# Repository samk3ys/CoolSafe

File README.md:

# Cool Safe
UKY capstone project

ECE 490 / 491 - 2 Semester Senior Design - Fall 2019 thru Spring 2020

Sponsor: GE Appliances, a Haier Company 
Contact: Choon Jae-Ryu (ChoonJae.Ryu@geappliances.com)

Members: 
  Sam Keys (CPE) 
  Shae Henry (EE) 
  Steven Deaton (EE) 
  Sylvester Okafor (EE) 
  Tylor Mendez (CPE)

Project Summary: 
  Multi-generational living has driven a need for a safe storage for medications in the home. This project aims to develop a lock-bin for use in a refrigerator that is only accessible thru a biometric identification (or physical key for backup). Also to create a mobile app that can display authorized users and add / delete / disable these users.

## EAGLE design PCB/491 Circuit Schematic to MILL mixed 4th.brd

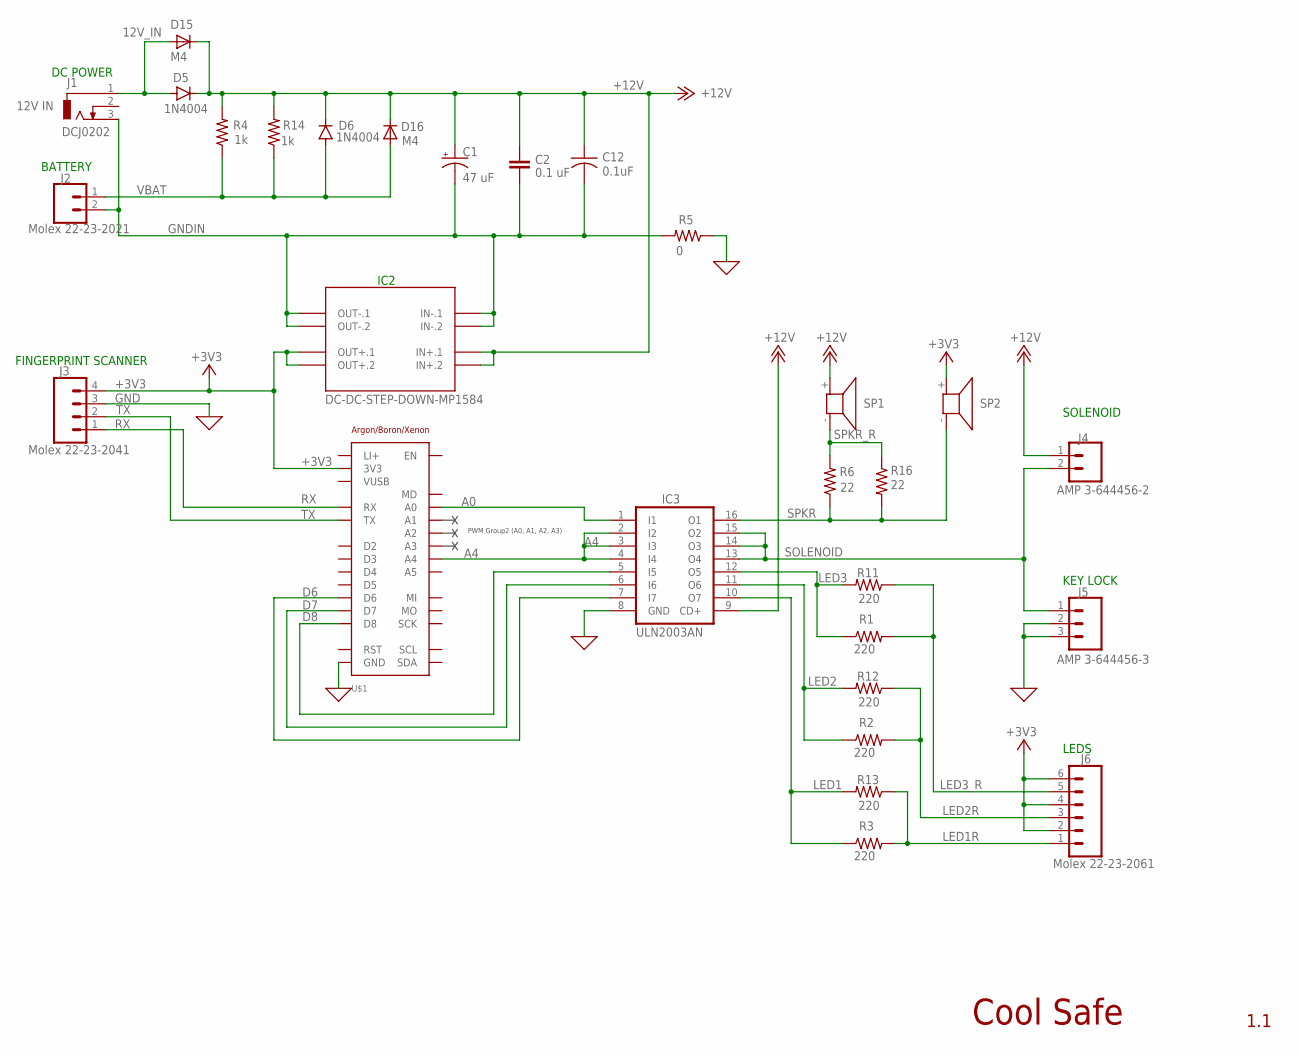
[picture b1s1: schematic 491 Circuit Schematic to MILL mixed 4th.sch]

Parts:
C1: 47 uF; E2,5-6
C2: 0.1 uF; C2.5-5
C12: 0.1uF; C1206
D5, D6: 1N4004; DO41-10
D15, D16: M4; SMA-DO214AC
IC2: DC-DC-STEP-DOWN-MP1584
IC3: ULN2003AN; DIL16
J1: DCJ0202
J2: Molex 22-23-2021; MOLEX-1X2
J3: Molex 22-23-2041; MOLEX-1X4
J4: AMP 3-644456-2; 1X02
J5: AMP 3-644456-3; 1X03
J6: Molex 22-23-2061; MOLEX-1X6
R1, R2, R3: 220; 0207/10
R4: 1k; 0207/10
R5: 0; 0207/10
R6: 22; 0204/7
R11, R12, R13: 220; M1206
R14: 1k; M1206
R16: 22; M1206
SP1, SP2: KSS1201
U$1: TEMPLATE_ARGON/BORON/XENONPTH; NO_PADS

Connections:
12V_IN: D5.A, D15.A, J1.1
+3V3: IC2.OUT+.1, IC2.OUT+.2, J3.4, J6.2, J6.4, J6.6, SP2.+ (1), U$1.P$14 (3V3)
+12V: C1.+, C2.1, C12.1, D5.C, D6.C, D15.K (C), D16.K (C), IC2.IN+.1, IC2.IN+.2, IC3.9 (CD+), J4.1, R4.2, R14.2, SP1.+ (1)
A0: IC3.1 (I1), U$1.P$17 (A0)
A4: IC3.2 (I2), IC3.3 (I3), IC3.4 (I4), U$1.P$21 (A4)
D6: IC3.7 (I7), U$1.P$6 (D6)
D7: IC3.6 (I6), U$1.P$5 (D7)
D8: IC3.5 (I5), U$1.P$4 (D8)
GND: IC3.8 (GND), J3.3, J5.2, J5.3, R5.1, U$1.P$16 (GND)
GNDIN: C1.-, C2.2, C12.2, IC2.IN-.1, IC2.IN-.2, IC2.OUT-.1, IC2.OUT-.2, J1.3, J2.2, R5.2
LED1: IC3.10 (O7), R3.1, R13.2
LED1R: J6.1, R3.2, R13.1
LED2: IC3.11 (O6), R2.1, R12.2
LED2R: J6.3, R2.2, R12.1
LED3: IC3.12 (O5), R1.1, R11.2
LED3_R: J6.5, R1.2, R11.1
RX: J3.1, U$1.P$26 (RX)
SOLENOID: IC3.13 (O4), IC3.14 (O3), IC3.15 (O2), J4.2, J5.1
SPKR: IC3.16 (O1), R6.1, R16.2, SP2.- (2)
SPKR_R: R6.2, R16.1, SP1.- (2)
TX: J3.2, U$1.P$27 (TX)
VBAT: D6.A, D16.A, J2.1, R4.1, R14.1

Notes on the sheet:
PWM Group2 (A0, A1, A2, A3)
1.1
Cool Safe
12V IN
SOLENOID
KEY LOCK
LEDS
BATTERY
FINGERPRINT SCANNER
IC2
DC POWER

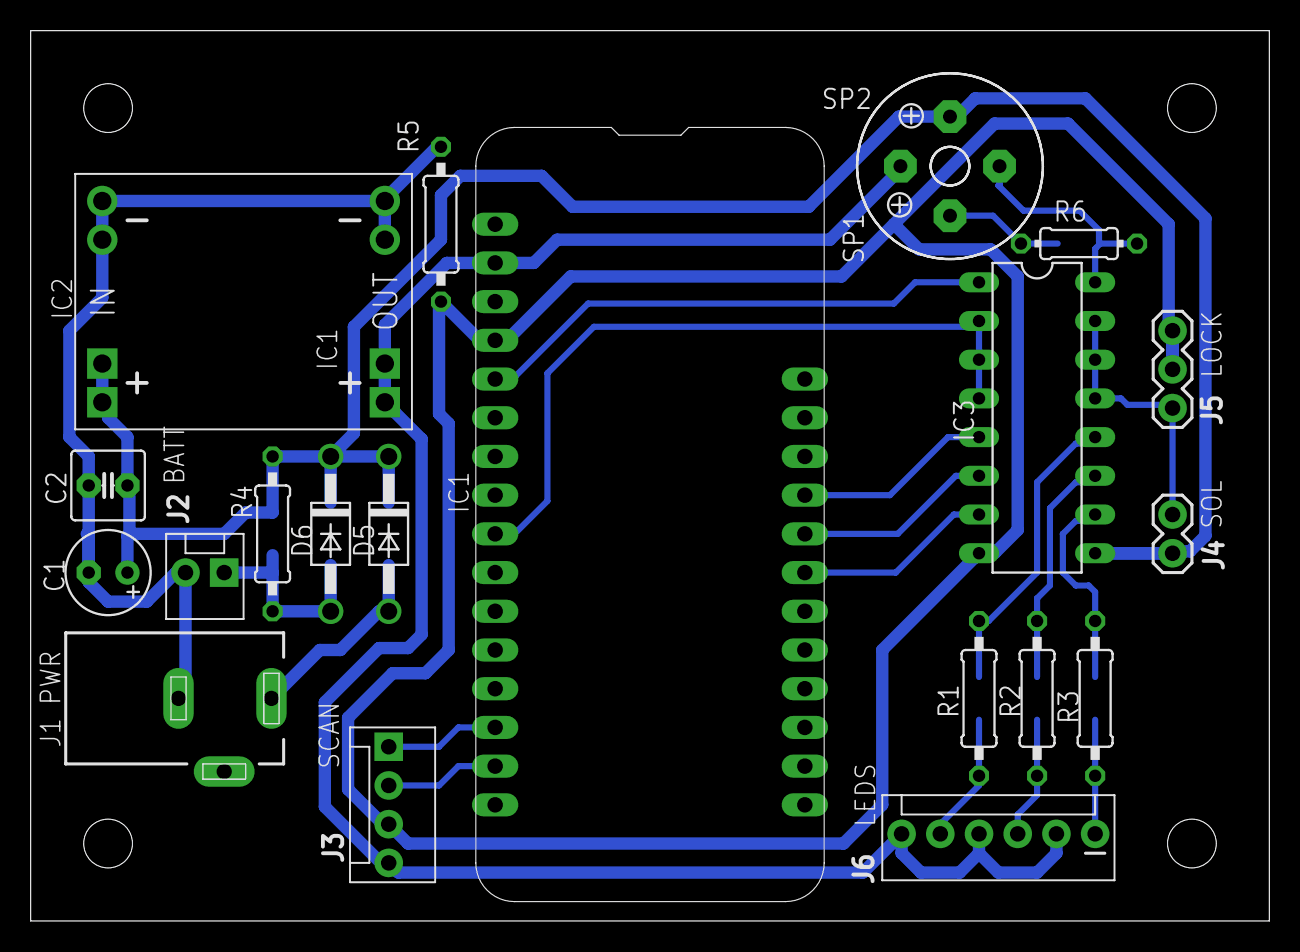
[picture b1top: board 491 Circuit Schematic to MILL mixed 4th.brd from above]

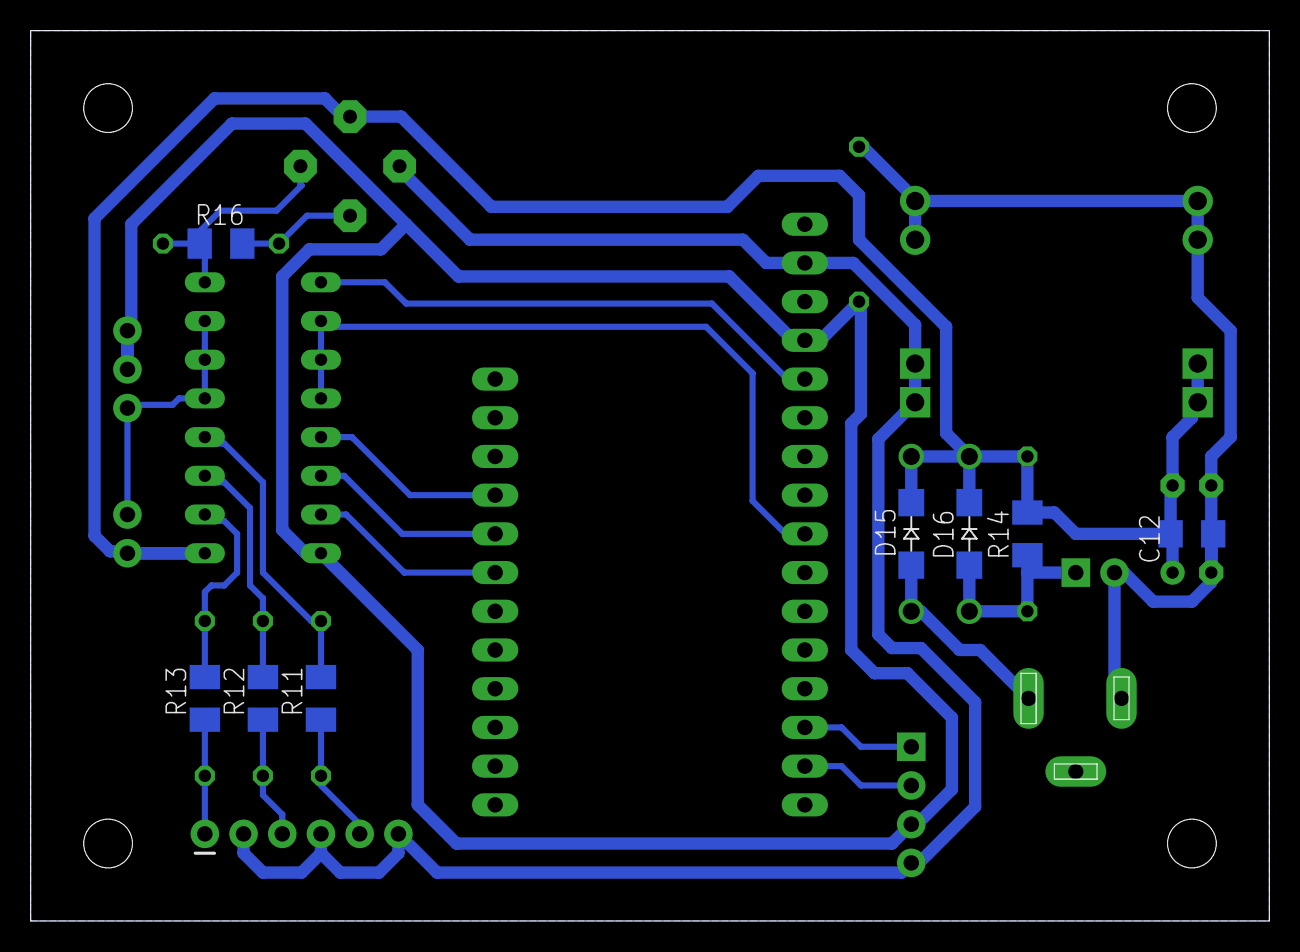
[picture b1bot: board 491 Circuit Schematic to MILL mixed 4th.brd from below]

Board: 2 copper layers, 81.3 x 58.4 mm, 29 parts (8 on the bottom side), 22 nets.

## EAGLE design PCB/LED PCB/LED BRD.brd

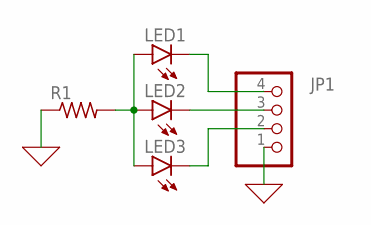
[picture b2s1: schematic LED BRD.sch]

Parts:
JP1: PINHD-1X4; 1X04
LED1, LED2, LED3: LED5MM
R1: R-US_0204/7; 0204/7

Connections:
0: JP1.1, R1.1
unnamed: LED1.A, LED2.A, LED3.A, R1.2
unnamed: JP1.2, LED3.K (C)
unnamed: JP1.4, LED1.K (C)
unnamed: JP1.3, LED2.K (C)

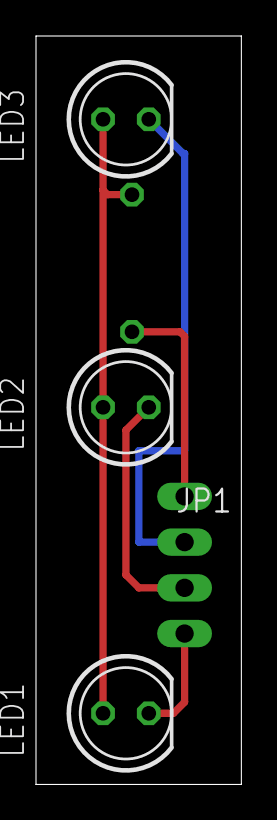
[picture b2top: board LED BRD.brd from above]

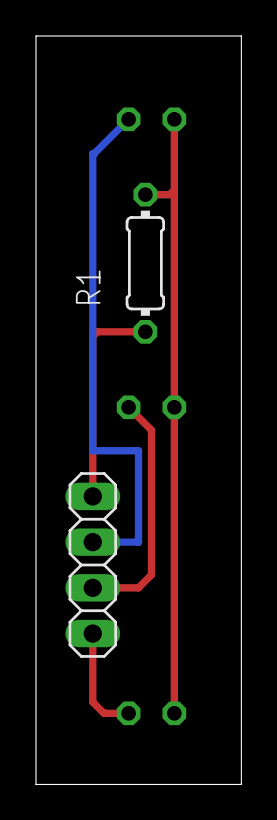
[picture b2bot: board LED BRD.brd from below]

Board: 2 copper layers, 11.4 x 41.6 mm, 5 parts (2 on the bottom side), 5 nets.

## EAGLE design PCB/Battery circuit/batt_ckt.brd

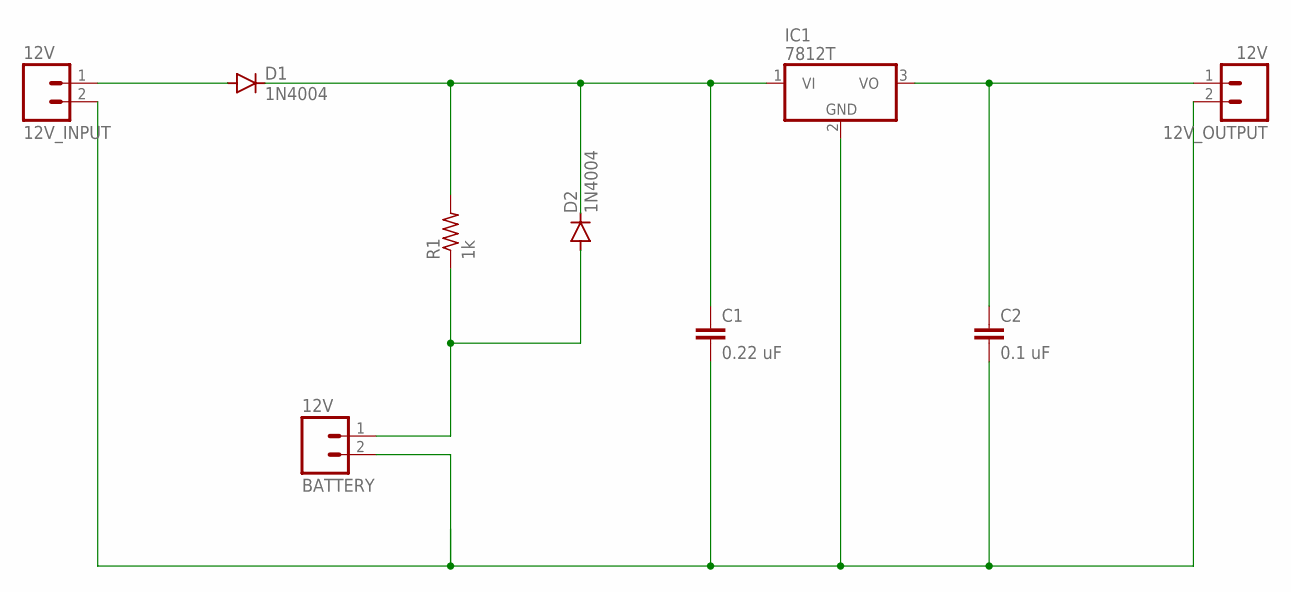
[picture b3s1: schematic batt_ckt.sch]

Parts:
12V_INPUT, 12V_OUTPUT: 12V; 02P
BATTERY: 12V; 02P
C1: 0.22 uF; C2.5-5
C2: 0.1 uF; C2.5-5
D1, D2: 1N4004; DO41-10
IC1: 7812T; TO220H
R1: 1k; 0207/10

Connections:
unnamed: BATTERY.1, D2.A, R1.1
unnamed: C1.1, D1.C, D2.C, IC1.1 (VI), R1.2
unnamed: 12V_INPUT.1, D1.A
unnamed: 12V_INPUT.2, 12V_OUTPUT.2, BATTERY.2, C1.2, C2.2, IC1.2 (GND)
unnamed: 12V_OUTPUT.1, C2.1, IC1.3 (VO)

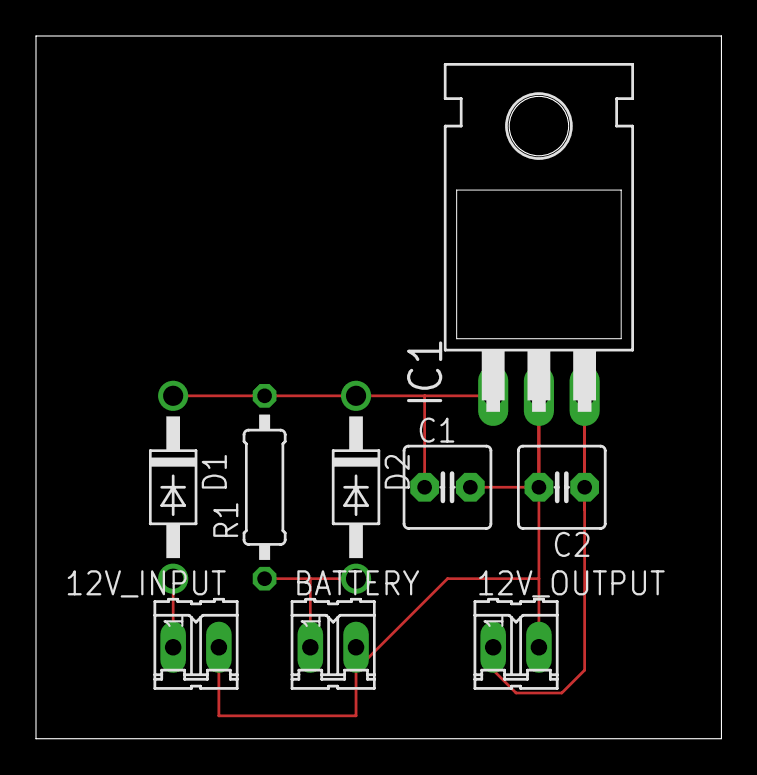
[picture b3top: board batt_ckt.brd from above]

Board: 2 copper layers, 38.1 x 39.0 mm, 9 parts (0 on the bottom side), 5 nets.

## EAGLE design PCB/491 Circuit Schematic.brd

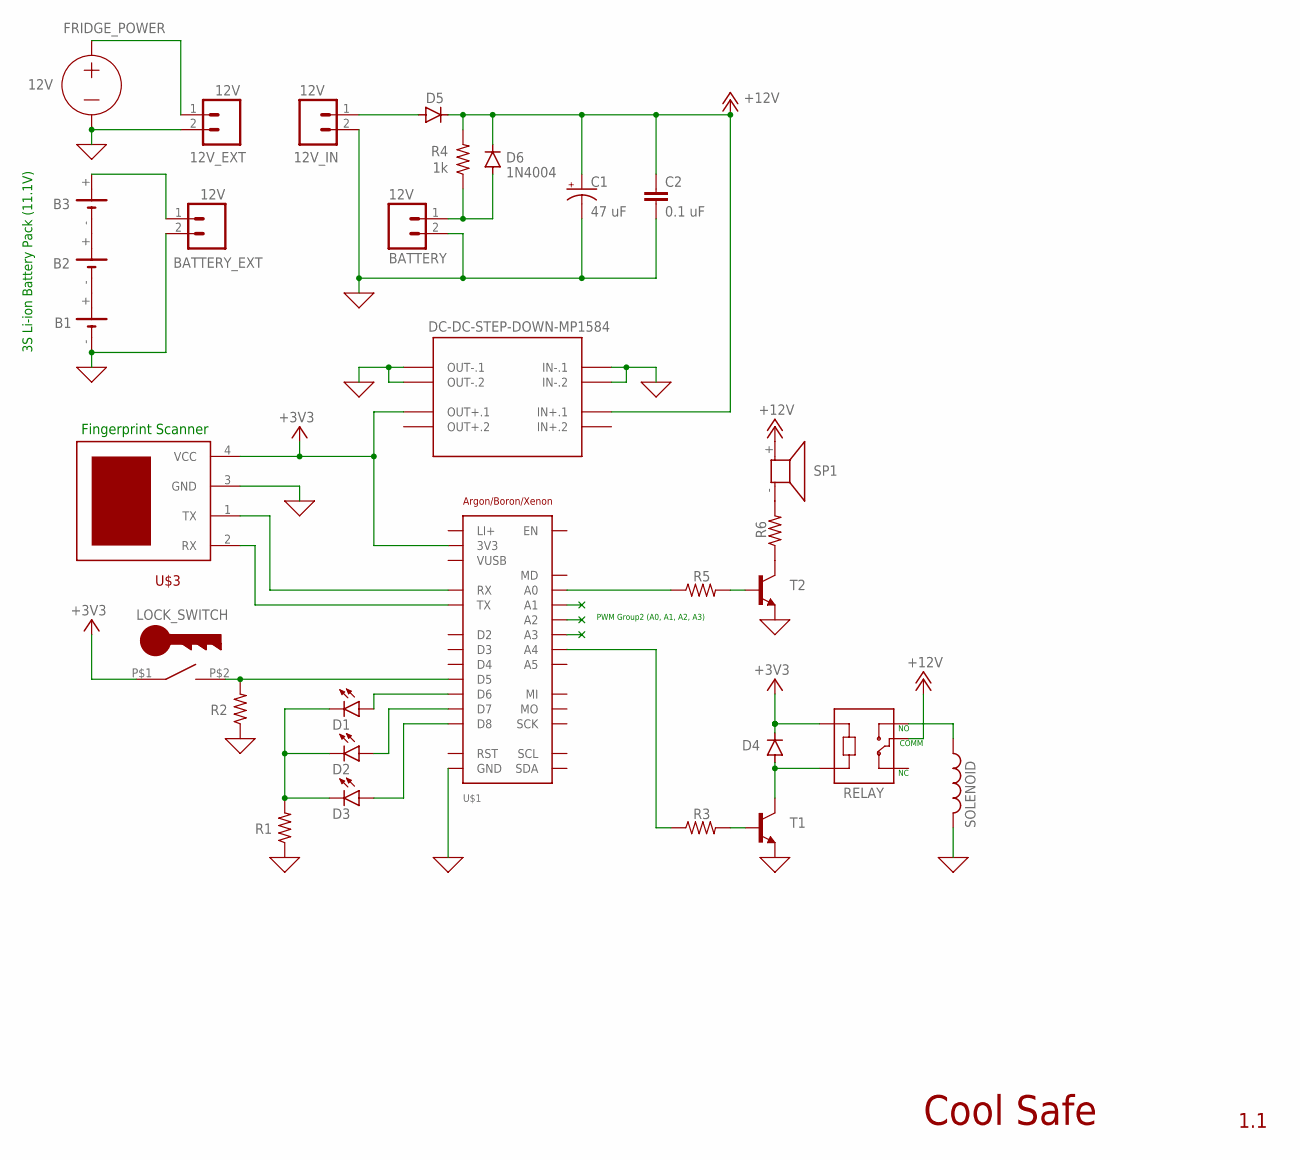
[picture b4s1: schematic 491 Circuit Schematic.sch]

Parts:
12V_EXT, 12V_IN: 12V; 02P
B1, B2, B3: SL-340/P3.6V
BATTERY: 12V; 02P
BATTERY_EXT: 12V; 02P
C1: 47 uF; E2,5-6
C2: 0.1 uF; C2.5-5
D1, D2, D3: U57X32
D4, D5, D6: 1N4004; DO41-10
L2: SOLENOID; 0207/5V
LOCK_SWITCH: LOCK_SWITCH; SWITCH_TERMINAL
R1, R2, R3, R5, R6: R-US_0204/7; 0204/7
R4: 1k; 0207/10
RELAY: SRD-05VDC-SL-C; RELAY_SRD-05VDC-SL-C
SP1: KSS1201
T1, T2: -NPN-TO92; TO92
U$1: TEMPLATE_ARGON/BORON/XENONFEATHER_ONLY; FEATHER_ONLY
U$2: DC-DC-STEP-DOWN-MP1584
U$3: FPS; JST

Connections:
0: 12V_EXT.2, 12V_IN.2, B1.-, BATTERY.2, BATTERY_EXT.2, C1.-, C2.2, L2.2, R1.1, R2.1, T1.1 (E), T2.1 (E), U$1.16B (GND), U$1.16T (GND), U$2.IN-.1, U$2.IN-.2, U$2.OUT-.1, U$2.OUT-.2, U$3.3 (GND)
+3V3: D4.C, LOCK_SWITCH.P$1, RELAY.A1, U$1.14B (3V3), U$1.14T (3V3), U$2.OUT+.1, U$3.4 (VCC)
FPS: R6.2, SP1.- (2)
unnamed: B2.+, B3.-
unnamed: R5.1, U$1.17B (A0), U$1.17T (A0)
unnamed: B1.+, B2.-
unnamed: D1.A, U$1.06B (D6), U$1.06T (D6)
unnamed: D2.A, U$1.05B (D7), U$1.05T (D7)
unnamed: D3.A, U$1.04B (D8), U$1.04T (D8)
unnamed: LOCK_SWITCH.P$2, R2.2, U$1.07B (D5), U$1.07T (D5)
unnamed: D1.K (C), D2.K (C), D3.K (C), R1.2
unnamed: D4.A, RELAY.A2, T1.3 (C)
unnamed: L2.1, RELAY.NO
unnamed: BATTERY.1, D6.A, R4.1
unnamed: U$1.26B (RX), U$1.26T (RX), U$3.1 (TX)
unnamed: R3.2, T1.2 (B)
unnamed: R3.1, U$1.21B (A4), U$1.21T (A4)
unnamed: U$1.18B (A1), U$1.18T (A1)
unnamed: U$1.19B (A2), U$1.19T (A2)
unnamed: U$1.20B (A3), U$1.20T (A3)
unnamed: U$1.27B (TX), U$1.27T (TX), U$3.2 (RX)
unnamed: 12V_IN.1, D5.A
unnamed: B3.+, BATTERY_EXT.1
unnamed: R6.1, T2.3 (C)

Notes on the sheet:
PWM Group2 (A0, A1, A2, A3)
COMM
Fingerprint Scanner
3S Li-ion Battery Pack (11.1V)
1.1
Cool Safe

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
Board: 2 copper layers, 28 parts (0 on the bottom side), 24 nets, no tracks yet.

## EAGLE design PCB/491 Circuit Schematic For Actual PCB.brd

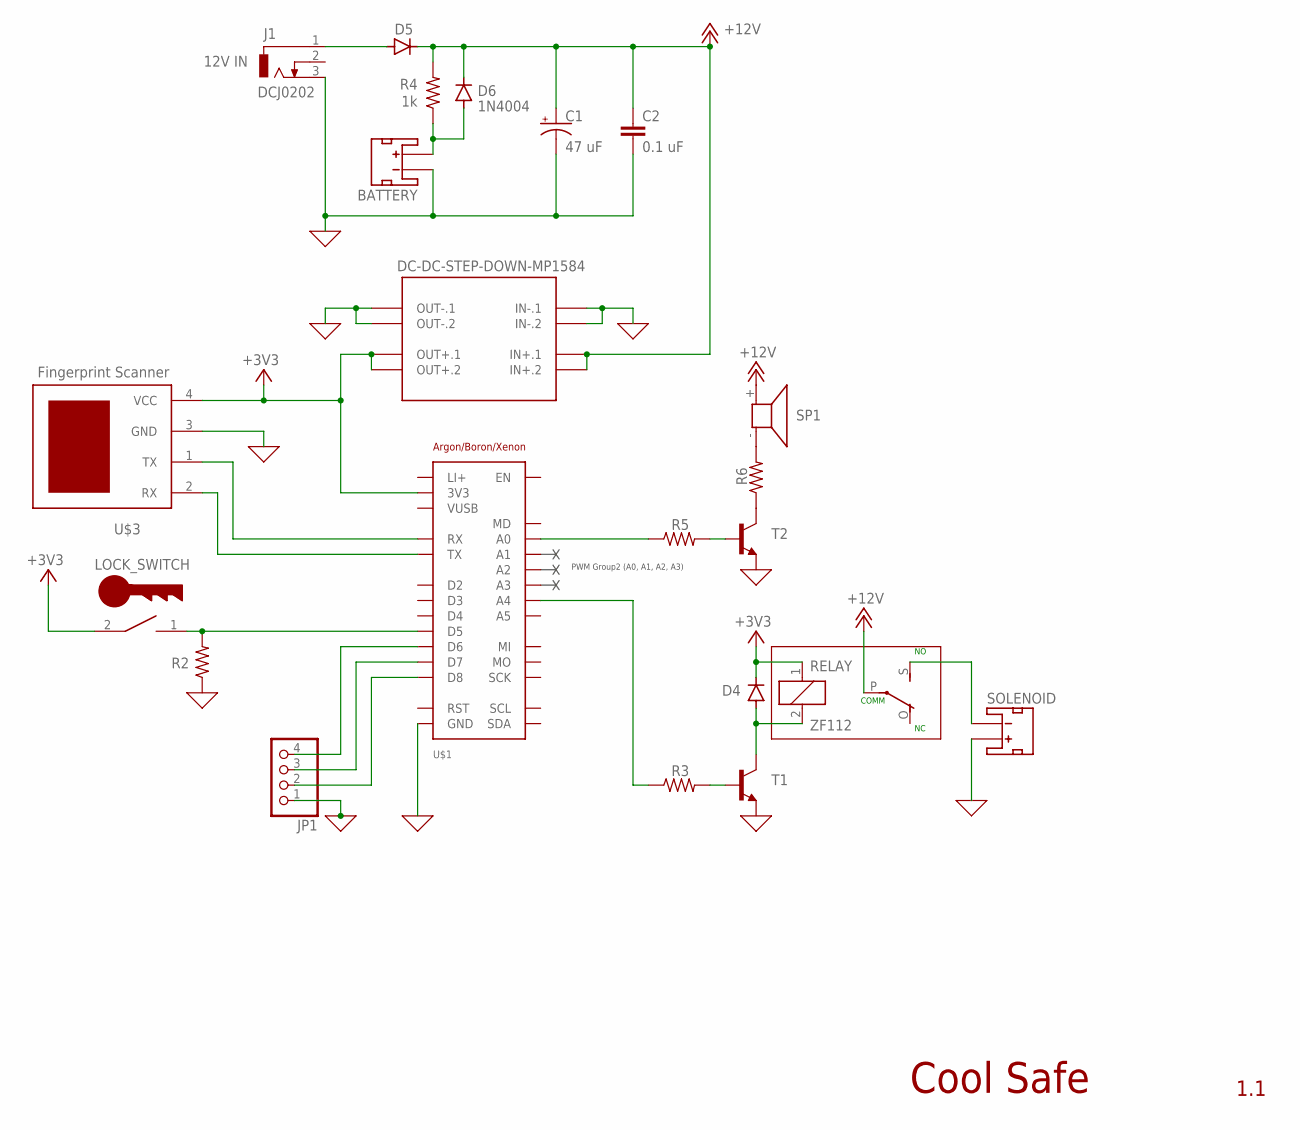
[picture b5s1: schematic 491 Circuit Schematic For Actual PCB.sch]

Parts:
BATTERY: JST_2MM_MALE; JST-2-SMD
C1: 47 uF; E2,5-6
C2: 0.1 uF; C2.5-5
D4, D5, D6: 1N4004; DO41-10
J1: DCJ0202
JP1: PINHD-1X4/90; 1X04/90
LOCK_SWITCH: LOCK_SWITCHSCREW_TERMINAL; 1751248
R2: R-US_0207/10; 0207/10
R3, R5, R6: R-US_0204/7; 0204/7
R4: 1k; 0207/10
RELAY: ZF112
SOLENOID: JST_2MM_MALE; JST-2-SMD
SP1: KSS1201
T1, T2: -NPN-TO92; TO92
U$1: TEMPLATE_ARGON/BORON/XENONFEATHER_ONLY; FEATHER_ONLY
U$2: DC-DC-STEP-DOWN-MP1584
U$3: FPSQWIIC; 1X04_1MM_RA

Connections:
0: BATTERY.1 (-), C1.-, C2.2, J1.3, JP1.1, R2.1, SOLENOID.2 (+), T1.1 (E), T2.1 (E), U$1.16B (GND), U$1.16T (GND), U$1.P$16 (GND), U$2.IN-.1, U$2.IN-.2, U$2.OUT-.1, U$2.OUT-.2, U$3.3 (GND)
+3V3: D4.C, LOCK_SWITCH.2, RELAY.1, U$1.14B (3V3), U$1.14T (3V3), U$1.P$14 (3V3), U$2.OUT+.1, U$2.OUT+.2, U$3.4 (VCC)
+12V: C1.+, C2.1, D5.C, D6.C, R4.2, RELAY.P, SP1.+ (1), U$2.IN+.1, U$2.IN+.2
unnamed: BATTERY.2 (+), D6.A, R4.1
unnamed: R5.2, T2.2 (B)
unnamed: R5.1, U$1.17B (A0), U$1.17T (A0), U$1.P$17 (A0)
unnamed: JP1.4, U$1.06B (D6), U$1.06T (D6), U$1.P$6 (D6)
unnamed: JP1.3, U$1.05B (D7), U$1.05T (D7), U$1.P$5 (D7)
unnamed: JP1.2, U$1.04B (D8), U$1.04T (D8), U$1.P$4 (D8)
unnamed: LOCK_SWITCH.1, R2.2, U$1.07B (D5), U$1.07T (D5), U$1.P$7 (D5)
unnamed: D4.A, RELAY.2, T1.3 (C)
unnamed: RELAY.S, SOLENOID.1 (-)
unnamed: R6.1, T2.3 (C)
unnamed: U$1.26B (RX), U$1.26T (RX), U$1.P$26 (RX), U$3.1 (TX)
unnamed: R3.2, T1.2 (B)
unnamed: R3.1, U$1.21B (A4), U$1.21T (A4), U$1.P$21 (A4)
unnamed: U$1.27B (TX), U$1.27T (TX), U$1.P$27 (TX), U$3.2 (RX)
unnamed: D5.A, J1.1
unnamed: R6.2, SP1.- (2)

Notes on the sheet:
PWM Group2 (A0, A1, A2, A3)
COMM
Fingerprint Scanner
1.1
Cool Safe
12V IN

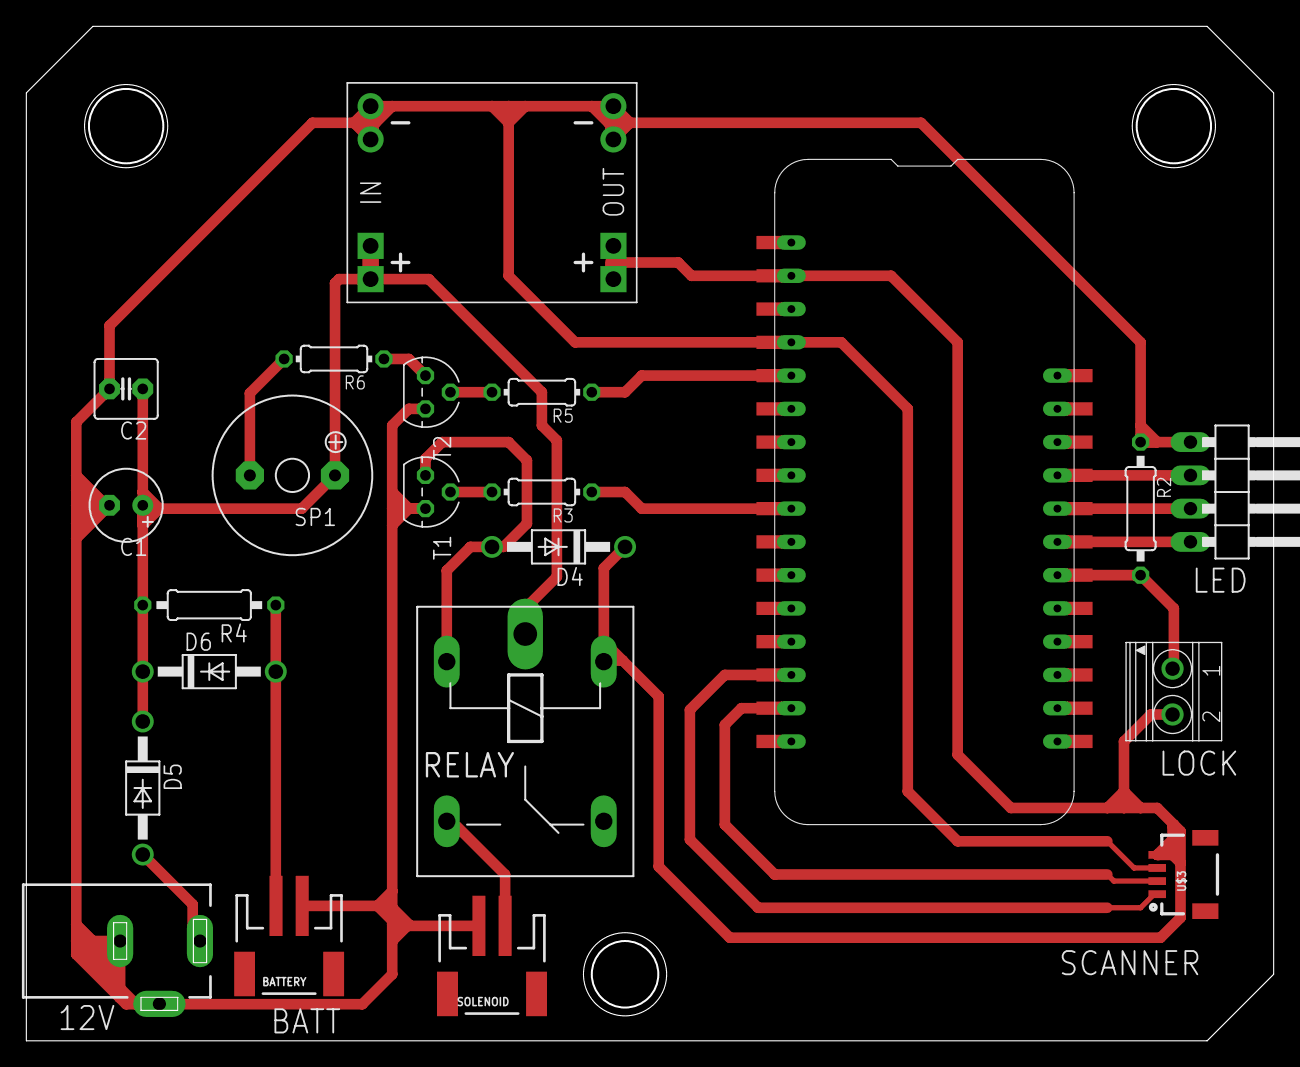
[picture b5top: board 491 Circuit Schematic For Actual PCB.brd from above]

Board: 2 copper layers, 95.2 x 77.5 mm, 22 parts (0 on the bottom side), 19 nets.

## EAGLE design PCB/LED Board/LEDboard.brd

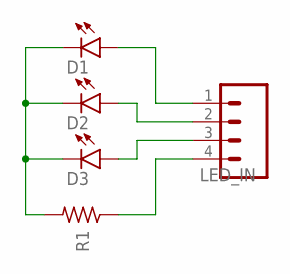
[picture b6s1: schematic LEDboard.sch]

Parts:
D1, D2, D3: LED5MM
LED_IN: M04; 04P
R1: R-US_0204/7; 0204/7

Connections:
unnamed: D3.A, LED_IN.3
unnamed: D2.A, LED_IN.2
unnamed: D1.A, LED_IN.1
unnamed: D1.K (C), D2.K (C), D3.K (C), R1.2
unnamed: LED_IN.4, R1.1

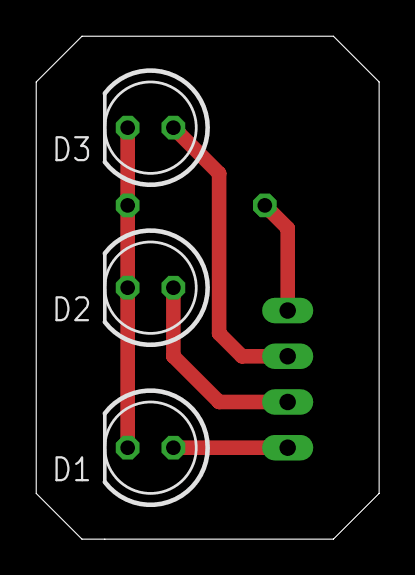
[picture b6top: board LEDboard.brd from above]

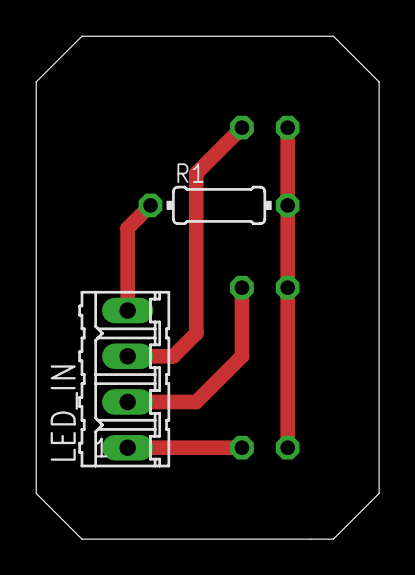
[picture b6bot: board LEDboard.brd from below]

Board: 2 copper layers, 19.1 x 27.9 mm, 5 parts (2 on the bottom side), 5 nets.

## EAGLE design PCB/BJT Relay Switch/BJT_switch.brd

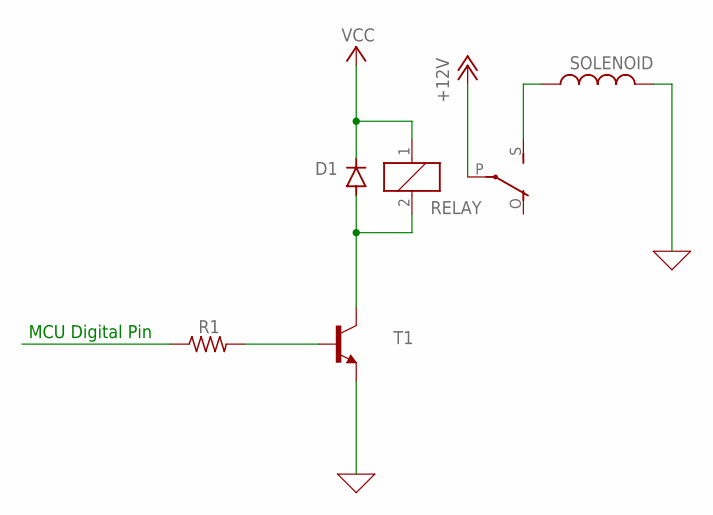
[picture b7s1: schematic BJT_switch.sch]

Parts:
D1: 1N4004; DO41-10
L1: SOLENOID; 0207/5V
R1: R-US_0204/7; 0204/7
RELAY: ZF112
T1: -NPN-TO92; TO92

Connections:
0: L1.2, T1.1 (E)
+12V: RELAY.P
unnamed: L1.1, RELAY.S
unnamed: R1.2, T1.2 (B)
unnamed: D1.A, RELAY.2, T1.3 (C)
VCC: D1.C, RELAY.1

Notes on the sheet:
MCU Digital Pin

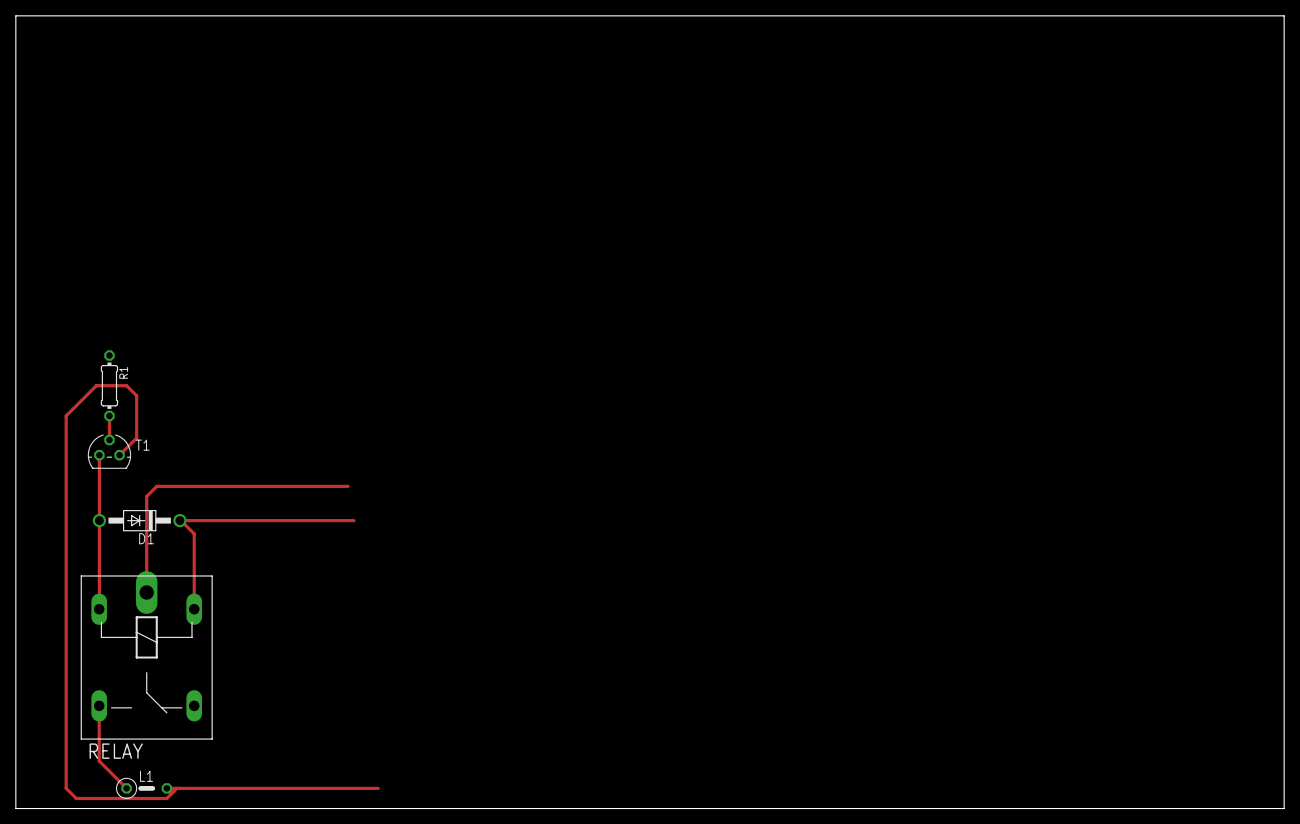
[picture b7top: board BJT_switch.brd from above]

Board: 2 copper layers, 160.0 x 100.0 mm, 5 parts (0 on the bottom side), 5 nets.

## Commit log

2020-02-09 Some Particle examples
    From my desktop. BLE and Serial examples.
2020-02-09 Print BLE input to USB Serial
2020-02-09 Added Flutter Demo from Fall
2020-02-15 BLE Particle update
    BLE Serial terminal can change LED colors. a=red, b=green, c=blue, anything else=yellow.
2020-02-15 Add files via upload
    What I've got so far of the app.. still a work in progress...for the error at line 165 (if there) can be fixed by removing the if statement there it just won't be doing what I am trying to get work
2020-02-16 SoftwareSerial Fix
    Instead of trying to use two non-UART digital pins the FPS_GT511C3 library now uses the Serial1 pins. They are labeled Rx and Tx on the Particle Xenon and are pins 14 and 15 respectively. The new lib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
2020-02-17 BLE_Demo update
    Send an RGB Hex code to the xenon to change the on-board LED to that color
2020-02-18 project uploaded
    replaced my "just the main file" with the whole folder used by android studio
2020-02-23 Several small changes
    FPS library now called "FPS_GT511C3_Particle" instead of "FPS_GT511C3_Xenon". Other changes to BLE demo.
2020-02-23 EE490_test2.ino to its own folder.
    Seperately changed the include in the fps library cpp file to reflect the changed name.
2020-02-24 Play tones w/ buzzer
    Startup sound, good sound, bad sound, Mario, Doom, & Tetris
2020-02-25 Update Startup_namer.dart
    only thing app needs now is individual functions completed and "registration mode" windows.
2020-02-27 Create FPS CODE
2020-02-29 Reorganize files
    Files at root are now in proper directories. "Flutter" directory renamed "Mobile App". "Particle" directory renamed "Microcontroller".
2020-02-29 Added EAGLE PCB Folder
    Includes sch and brd files and a library of custom parts
2020-02-29 PCB Update
    Added FPS and Voltage Regulator.
2020-03-01 PCB V1
2020-03-05 added fps with mcu code
2020-03-05 Create 491 Circuit Schematic For Actual PCB.sch
    New PCB schematic for actual PCB
2020-03-07 Edited Schematic, started layout
2020-03-07 Added 5mm LEDs
2020-03-08 Update to PCB
2020-03-08 PCB V1
    Pretty much ready to mill. Added a to MILL board and some breakout boards for SMT components so that we only need a single-sided copper clad board.
2020-03-09 PCB Edit
    Ready for milling
2020-03-10 JST Battery Connector
    Changed battery connector from a screw terminal to a JST connector to make sure it gets plugged in correctly.
2020-03-10 Added LED PCB
2020-03-26 Updated
    Minor changes from laptop
2020-03-27 App mostly done
    just need to integrate with BLE and maybe add a few lines here and there
2020-04-01 Minimally working
    PCB put together and most functionality tested. FPS and Key both activate solenoid. Sounds play. Still need to integrate BLE.
2020-04-02 Key only unlocks bin once
    Some general clean-up. Made IdentifyUser() a function for identifying a user with the FPS. Modified main loop so that the key only unlocks the bun once by adding a flag to keep track of when the key'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
2020-04-02 Added startup LED sequence
    Turns all external LEDs on at boot-up to make sure they work. Goes on and off in a wave green -> amber -> red. Then the startup sound plays to let the user know the system is ready to use
2020-04-04 Manual enrollment option
    If you turn the key switch on and off quickly (~500 ms) then the system will enter registration mode to enroll a new fingerprint
2020-04-08 60 sec enroll timeout
    The system will only wait for fingerprints enrollment for a minute, then resume normal operation if nothing shows up in that time.
2020-04-08 FPS Library name change
    Changed from legacy GT511C3 to name of the FPS we're actually using (GT5521F32)
2020-04-11 Enrollment scans blink amber
    Changed code to blink amber LED instead of green after each scan during enrollment. Still blinks red or green to signify fail or success at the end of enrollment
2020-04-11 app finished (minus BLE code)
    there are lines including "----BLE CODE" where some would go in future (mostly for transferring/recieving data)
2020-04-17 Updated BLE code
    For easier use from 3rd party BLE terminal mobile app
2020-04-25 Removed extra directory
    CoolSafe/Flutter/hello_flutter/lib
2020-05-05 EE 569 PCB
    Improved design with help from John Barnes
2020-07-17 Updated MCU code
    Final update from Sam. Includes a version without BLE as a good base for future development.

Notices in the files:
parts and their libraries:
SparkFun-Connectors: Licensing: Creative Commons ShareAlike 4.0 International - https://creativecommons.org/licenses/by-sa/4.0
